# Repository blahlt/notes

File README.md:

[WIKI](https://github.com/blahlt/notes/wiki)

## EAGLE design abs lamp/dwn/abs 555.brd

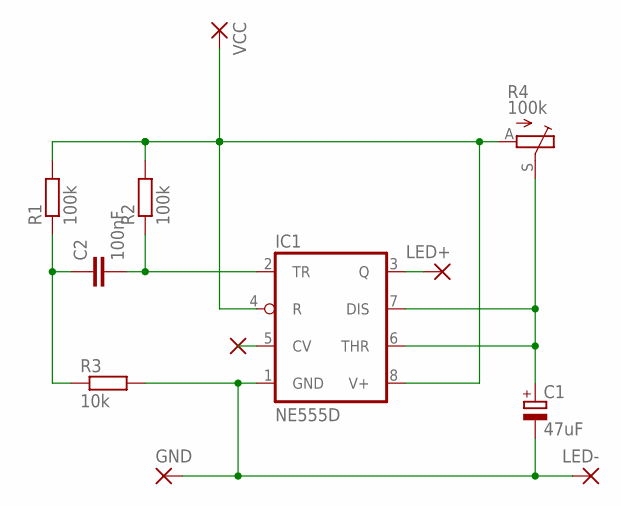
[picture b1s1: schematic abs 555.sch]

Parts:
C1: 47uF; D/7343-31W
C2: 100nF; C0805
GND: 2,54/0,8
IC1: NE555D; SO08
LED+: 2,54/0,8
LED-: 2,54/0,8
NC: 0.1MMPAD; PADS
R1, R2: 100k; R0805
R3: 10k; R0805
R4: 100k; CA6V
VCC: 2,54/0,8

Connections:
GND: C1.-, GND.1, IC1.1 (GND), LED-.1, R3.2
unnamed: C2.2, IC1.2 (TR), R2.1
unnamed: C2.1, R1.1, R3.1
unnamed: IC1.5 (CV), NC.1
unnamed: C1.+, IC1.6 (THR), IC1.7 (DIS), R4.S
unnamed: IC1.3 (Q), LED+.1
V+: IC1.4 (R), IC1.8 (V+), R1.2, R2.2, R4.A, VCC.1

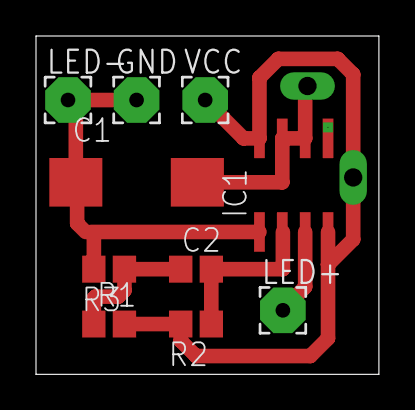
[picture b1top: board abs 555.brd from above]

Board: 2 copper layers, 19.1 x 18.8 mm, 12 parts (1 on the bottom side), 7 nets.

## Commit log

2013-07-28 software & img
2013-08-23 arduino dfu img and dwn
2013-08-26 arduino isp img & dwn
2013-09-12 scheme img
2013-09-17 lcd img
2014-01-13 atmega8 image
2014-01-30 atmega usb and stellaris images
2014-05-12 atmega8 isp scheme
2014-05-12 stellaris logic analyser
2014-12-20 new image
2014-12-21 new images
2014-12-21 readme fix
2014-12-22 esp8266 images
2014-12-22 new esp8266 image
2014-12-29 esp8266 image fix
2014-12-30 esp8266 http server images
2015-03-17 stm32f103c8t6 images
2015-04-12 rpi2 pinout image
2015-06-19 abs lamp
2015-06-19 abs img
2015-09-27 stm24f103c8t6 downloads
2015-09-27 nrf24l01+ images
2016-02-21 fake file
2016-02-21 remove fake file
2016-02-21 stm32f7disco img folder
2016-02-21 stm32f7disco image
2016-03-24 Create temp
2016-03-24 Added files via upload
2016-07-20 stm8s103f3p6 download files
2016-07-20 stm8s103f3p6 image
2016-07-20 resize stm8s103f3p6 image
2016-07-20 stm8flash path fix
2016-07-20 added sdcc file
2016-09-24 pcb images
2016-09-26 added stm32f103 pinout image
2016-09-26 added stm32f103 pinout pdf diagram
2016-09-29 stlinkv2 update images
2018-12-02 Create tmp
